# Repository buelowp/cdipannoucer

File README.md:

# Cobalt Digigal IP turnout control state announcer
The goal of this project is to provide a simple mechanism to report the realtime state of a Cobal Digital IP turnout control motor to loconet. For brevity, Cobalt Digital IP is reduced to CDIP in my work.

## Design
The Cobalt motor is really nice, it's a self contained DCC design and is reasonably robust. Not the quietest, but it works, and it works well with Digitrax and JMRI. However, because it's DCC only, JMRI has no mechanism for requesting state from the motor. This means, at startup, or if something outside of Loconet changes the turnout state, JMRI does not know that it happened. I like it when I see my layout in JMRI in the correct state. I have a 4 turnout cross over and two turnouts which gate reverse loops which are automated

So, basically, I chose this as a low impact HW/SW project I could do to solve the problem. I'm learning how to do HW as a long term software engineer by trade, and enjoy doing small projects with MCU's. This may not be very useful to very many people, but it's fun and I'm looking forward to using it on my layout which has about 30 turnouts in a 19'x19' snaking layout.

This will not do loconet forwarding, and you can't daisy chain. I started to think for the cost, it's pry just smarter to use a UP7 without the faceplate which gives you 4 reliable ports for ~16USD. While adding the HW here would have been cheaper, the cost and complexity made it less interesting to me. I may put it back in later as I get better a loconet circuitry. I removed the daisy chain option, even though that's effectively free, as you can't infinitely chain non boosted devices together, and I didn't want to keep track of how many were connected.

This design makes use of Seeed Studio XIAO modules. I love these things. They are pretty cheap overall, tiny, and you can swap different modules on the same carrier. So, my design uses the Pico MCU because I don't want to include WiFi in my design. My basement layout is pretty far from the nearest router, and I don't want to suck up a lot of the router's attention for these when turned on. However, without changing the hardware, or changing the board size, anyone could use the ESP32 if they choose to. The benefit there might be MQTT and adding a webserver to assign DCC addresses without recompiling the firmware.

While not yet coded up, my mechanism for knowing when to send a startup message will be based on the first Loconet traffic the board sees. As this can be DCC powered, it can also be DC powered, so triggering on when we start to see traffic would be the most beneficial in all cases.

## Requirements
* Provide Loconet messages for turnout state changes as they happen
* Provide a loconet message indicating turnout state on DCC power up
* Handle four turnouts on one board
* Run with either an ESP32 or RPi Pico
* Not require more than 8 GPIO (this one currently only uses 7, three are just there not doing much)
* Wide input voltage range
* Allow for direct connection of indicator LEDs for the turnout.
    * This allows to wire up signals as an example, without the need for extra diodes/resistors along the wire run.

### What it doesn't currently do
* Will not switch the turnout via a Loconet message
* Does not have a second Loconet port for daisy chain

## KiCad design
This is a work in progress. What I've got posted now is version 2, not yet ordered.

I built a first board based solely on a few simple schematic facts hoping they all sort of would just work. This did allow me to test the GPIO portion of the design and validate my assumptions were correct. However, version 1, which is not in git unforunately, did not work for Loconet traffic. I don't know why, but I did make a mistake in the pin assigments for the second Serial port on the XIAO Pico module. I did jumper it, but it still doesn't work. I also didn't add test points, so it's not possible for me at home to use a scope to figure out what's going on. All of those facts are fixed in the current version.

Recently, I also added the ability to use DCC for power. However, I couldn't find a way to combine the two DCC connectors at that point, so you always need a DCC input for the IO, but if you want to power via DCC, then you simply plug a DCC bus into the power connection. For this reason, that connection is no longer polarized, and it doesn't matter which way you wire it.

I also added 3 pins connected to D8, D9, and D10 in Arduino land. They have both Ground and Power pins to go with, so you can use them however you feel the urge. I would limit any GPIO access to 30ma total though, as you have 500ma from the board, but roughly 200ma is already consumed.

## KiCad notes
This design makes use of JLCPCB to source and order. The parts are identified in the BOM, and the parts that can't be assembled by JLCPCB are marked as such (the red X). I used a plugin to get the parts from

https://github.com/CDFER/JLCPCB-Kicad-Library

Which cannot at this time be installed automatically. Follow the directions on the README.

I also use the JLCPCB Fab extension which can be installed directly from the Extensions dialog.

# Notes
* The orientation of the DCC inputs into the Digital IP does matter. I assume for this device that DCC Rail A as labeled coming out of a Digitrax command station is the outer most pin 1 in the diagram below. If you reverse and put DCC Rail B into that slot, you either have to reverse Rail A and B inputs for the DCC Input terminal or update the code to account for the direction messages being backwards. Note, if you reverse using DCC address 197, you must also reverse the direction. This can be done by setting the CDIP inverted boolean to true.

* This is DC only, but takes up to 30V as input. The reason for this is that I have a 15V DC power bus running with the DCC bus to power some of the Digitrax devices in use (mostly PM74's). For the length of those conductors, even at 16Ga, you get some voltage drop and this should allow the boards to not worry about that.

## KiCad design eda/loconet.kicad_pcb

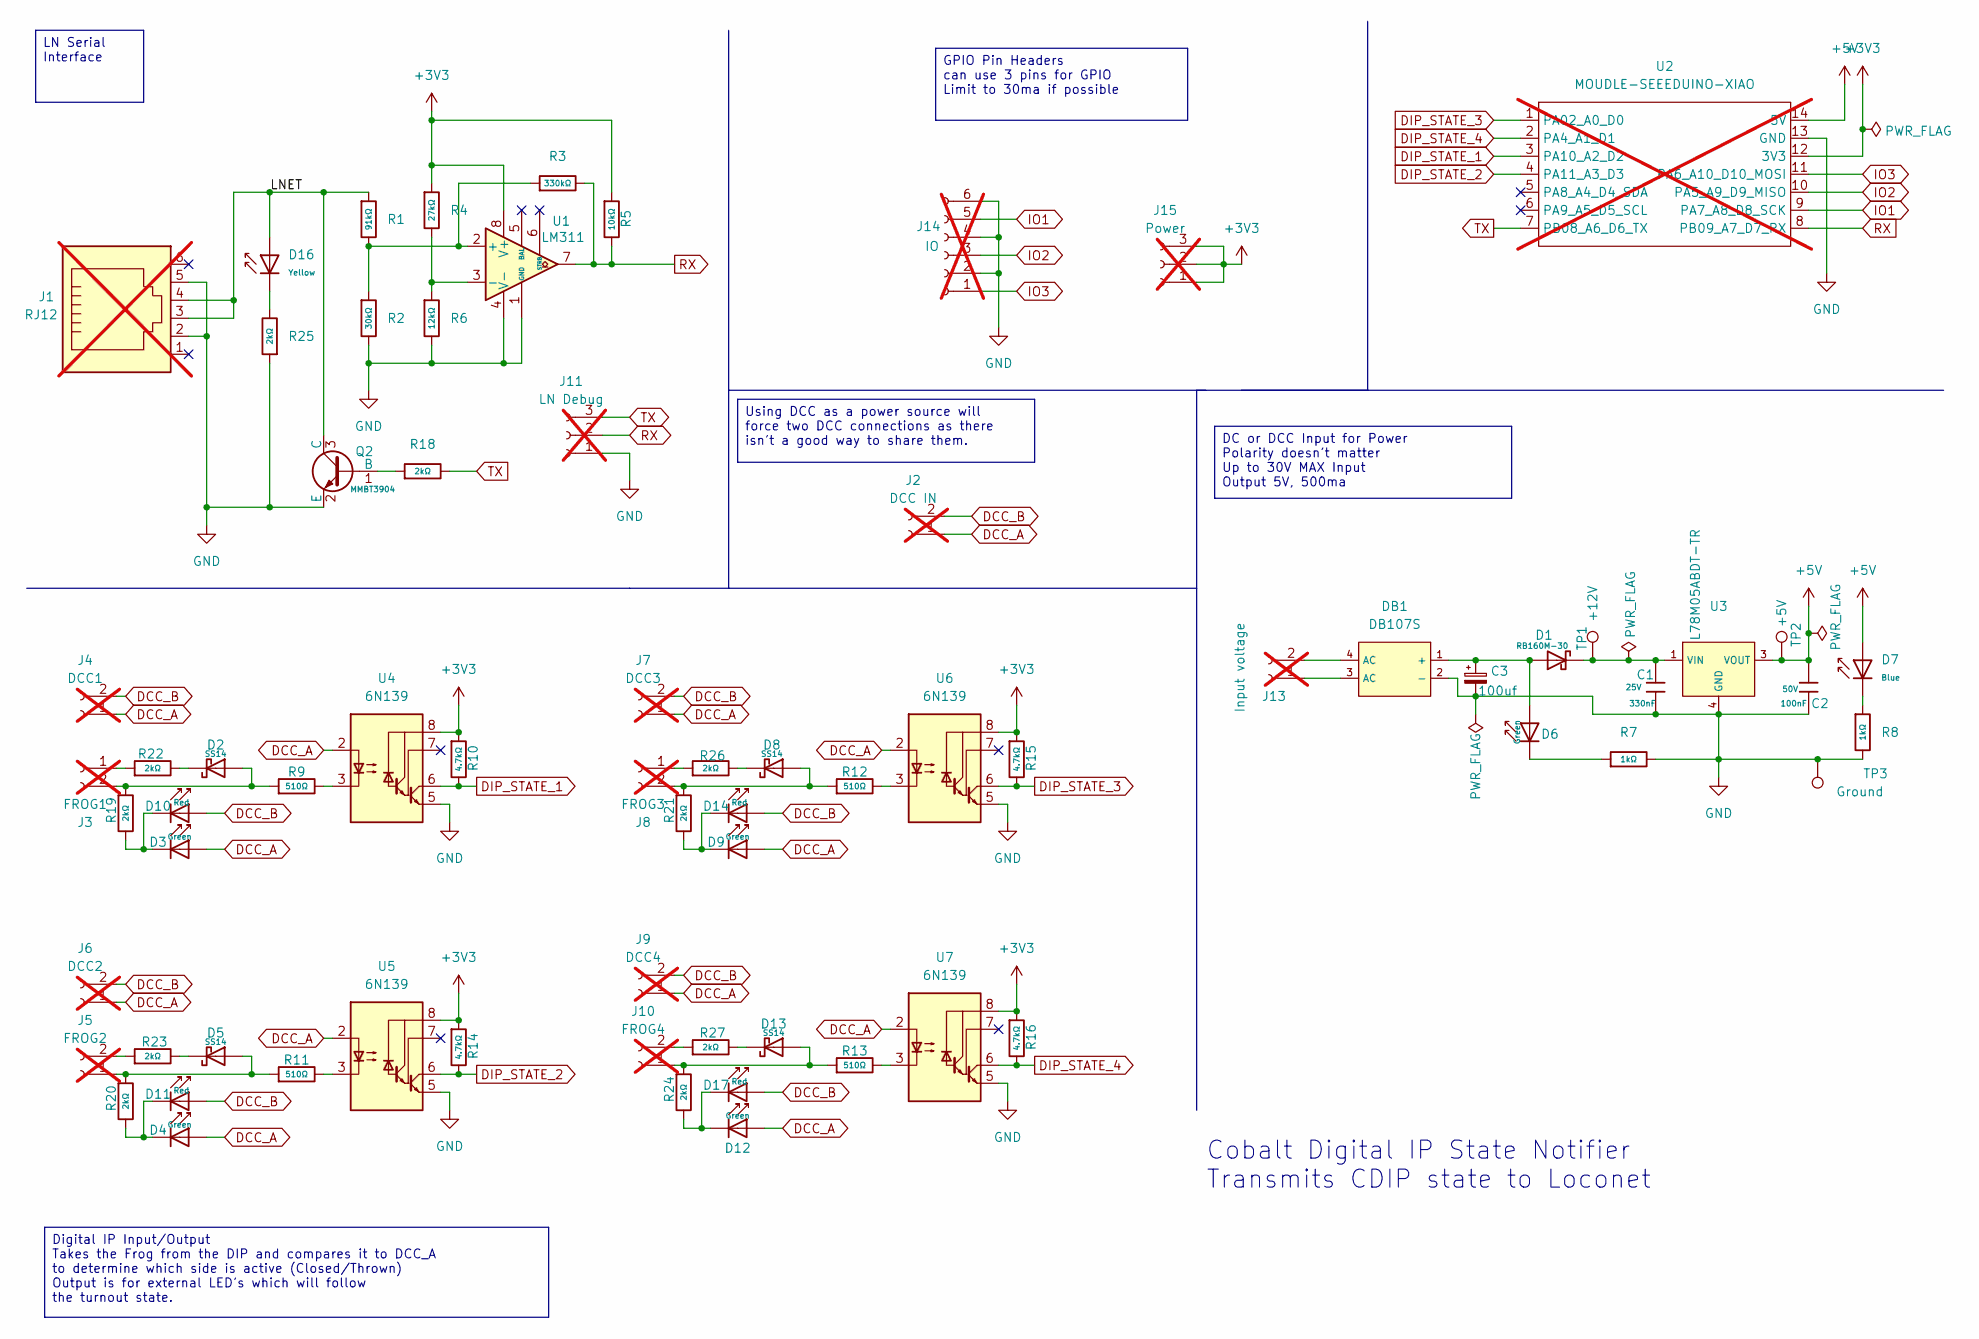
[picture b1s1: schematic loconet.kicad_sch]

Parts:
C1: 330nF; C_0603; Voltage Rated 25V; Tolerance ±10%; Part 0603B334K250NT; LCSC C1615
C2: 100nF; C_0603; Voltage Rated 50V; Tolerance ±10%; Part CC0603KRX7R9BB104; LCSC C14663
C3: 100uf; CP_Radial_D5.0mm_P2.50mm
D1: RB160M-30; D_SOD-123; Forward Voltage (Vf@If) 480mV@1A; Reverse Voltage (Vr) 30V; Part RB160M-30; LCSC C7502715
D2, D5, D8, D13: SS14; D_SMA; Forward Voltage (Vf@If) 550mV@1A; Reverse Voltage (Vr) 40V; Part SS14; LCSC C2480
D3, D4, D6, D9, D12: Green; D_0603; Part 19-217/GHC-YR1S2/6T; LCSC C2986059
D7: Blue; D_0603; Part 19-217/BHC-ZL1M2RY/6T; LCSC C2986058
D10, D11, D14, D17: Red; D_0603; Part KT-0603R; LCSC C2286
D16: Yellow; D_0603; Part 19-213/Y2C-CQ2R2L/3T(CY); LCSC C72038
DB1: DB107S; DBS_L8.2-W6.4-P5.10-LS10.0-BL; Reverse Voltage (Vr) 1kV; Forward Voltage (Vf@If) 1.1V@1A; Part DB107S; LCSC C5377
J1: RJ12; RJ25_Wayconn_MJEA-660X1_Horizontal; not fitted
J2: DCC IN; TerminalBlock_Phoenix_MKDS-1,5-2-5.08_1x02_P5.08mm_Horizont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; not fitted
J3: FROG1; TerminalBlock_Phoenix_MKDS-1,5-2-5.08_1x02_P5.08mm_Horizont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; not fitted
J4: DCC1; TerminalBlock_Phoenix_MKDS-1,5-2-5.08_1x02_P5.08mm_Horizont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; not fitted
J5: FROG2; TerminalBlock_Phoenix_MKDS-1,5-2-5.08_1x02_P5.08mm_Horizont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; not fitted
J6: DCC2; TerminalBlock_Phoenix_MKDS-1,5-2-5.08_1x02_P5.08mm_Horizont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; not fitted
J7: DCC3; TerminalBlock_Phoenix_MKDS-1,5-2-5.08_1x02_P5.08mm_Horizont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; not fitted
J8: FROG3; TerminalBlock_Phoenix_MKDS-1,5-2-5.08_1x02_P5.08mm_Horizont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; not fitted
J9: DCC4; TerminalBlock_Phoenix_MKDS-1,5-2-5.08_1x02_P5.08mm_Horizont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; not fitted
J10: FROG4; TerminalBlock_Phoenix_MKDS-1,5-2-5.08_1x02_P5.08mm_Horizont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; not fitted
J11: LN Debug; PinHeader_1x03_P2.54mm_Vertical; not fitted
J13: Input voltage; TerminalBlock_Phoenix_MKDS-1,5-2-5.08_1x02_P5.08mm_Horizont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; not fitted
J14: IO; PinHeader_2x03_P2.54mm_Vertical; not fitted
J15: Power; PinHeader_1x03_P2.54mm_Vertical; not fitted
Q2: MMBT3904; Q_SOT-23; Part MMBT3904; LCSC C7420353
R1: 91kΩ; R_0603; Overload Voltage (Max) 75V; Tolerance ±1%; Part 0603WAF9102T5E; LCSC C23265
R2: 30kΩ; R_0603; Overload Voltage (Max) 75V; Tolerance ±1%; Part 0603WAF3002T5E; LCSC C22984
R3: 330kΩ; R_0603; Overload Voltage (Max) 75V; Tolerance ±1%; Part 0603WAF3303T5E; LCSC C23137
R4: 27kΩ; R_0603; Overload Voltage (Max) 75V; Tolerance ±1%; Part 0603WAF2702T5E; LCSC C22967
R5: 10kΩ; R_0603; Overload Voltage (Max) 75V; Tolerance ±1%; Part 0603WAF1002T5E; LCSC C25804
R6: 12kΩ; R_0603; Overload Voltage (Max) 75V; Tolerance ±1%; Part 0603WAF1202T5E; LCSC C22790
R7, R8: 1kΩ; R_0402; Overload Voltage (Max) 50V; Tolerance ±1%; Part 0402WGF1001TCE; LCSC C11702
R9, R11, R12, R13: 510Ω; R_0603; Overload Voltage (Max) 75V; Tolerance ±1%; Part 0603WAF5100T5E; LCSC C23193
R10, R14, R15, R16: 4.7kΩ; R_0402; Overload Voltage (Max) 50V; Tolerance ±1%; Part 0402WGF4701TCE; LCSC C25900
R18, R22, R23, R25, R26, R27: 2kΩ; R_0402; Overload Voltage (Max) 50V; Tolerance ±1%; Part 0402WGF2001TCE; LCSC C4109
R19, R20, R21, R24: 2kΩ; R_0805; Overload Voltage (Max) 150V; Tolerance ±1%; Part 0805W8F2001T5E; LCSC C17604
TP1: +12V; TestPoint_Pad_1.5x1.5mm
TP2: +5V; TestPoint_Pad_1.5x1.5mm
TP3: Ground; TestPoint_Pad_1.5x1.5mm
U1: LM311; SOIC-8_L4.9-W3.9-P1.27-LS6.0-BL; LCSC C231850
U2: MOUDLE-SEEEDUINO-XIAO; MOUDLE14P-2.54-21X17.8MM; not fitted
U3: L78M05ABDT-TR; TO-252-2_L6.5-W6.1-P4.58-LS10.0-TL; Output Voltage 5V; Part L78M05ABDT-TR; LCSC C58069
U4, U5, U6, U7: 6N139; SOP-8_6.605x9.655mm_P2.54mm; LCSC C42186

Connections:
+3V3: J15.1, J15.2, J15.3, R4.1, R5.1, R10.1, R14.1, R15.1, R16.1, U1.8 (V+), U2.12 (3V3), U4.8 (VCC), U5.8 (VCC), U6.8 (VCC), U7.8 (VCC); also elsewhere on the board
+5V: C2.1, D7.2, TP2.1, U2.14 (5V), U3.3 (VOUT)
/LNET: D16.2, J1.3, J1.4, Q2.3 (C), R1.1
DCC_A: D3.2, D4.2, D9.2, D12.2, J2.1, J4.1, J6.1, J7.1, J9.1, U4.2 (C1), U5.2 (C1), U6.2 (C1), U7.2 (C1)
DCC_B: D10.2, D11.2, D14.2, D17.2, J2.2, J4.2, J6.2, J7.2, J9.2
DIP_STATE_1: R10.2, U2.3 (PA10_A2_D2), U4.6 (VO2)
DIP_STATE_2: R14.2, U2.4 (PA11_A3_D3), U5.6 (VO2)
DIP_STATE_3: R15.2, U2.1 (PA02_A0_D0), U6.6 (VO2)
DIP_STATE_4: R16.2, U2.2 (PA4_A1_D1), U7.6 (VO2)
GND: C1.2, C2.2, C3.2, DB1.2 (-), J1.2, J1.5, J11.1, J14.2, J14.4, J14.6, Q2.2 (E), R2.2, R6.2, R7.2, R8.2, R25.1, TP3.1, U1.1 (GND), U1.4 (V-), U2.13 (GND), U3.4 (GND), U4.5 (GND), U5.5 (GND), U6.5 (GND), U7.5 (GND)
IO1: J14.5, U2.9 (PA7_A8_D8_SCK)
IO2: J14.3, U2.10 (PA5_A9_D9_MISO)
IO3: J14.1, U2.11 (PA6_A10_D10_MOSI)
unnamed: D2.1, R22.2
unnamed: D5.1, R23.2
unnamed: D6.1, R7.1
unnamed: D7.1, R8.1
unnamed: D8.1, R26.2
unnamed: D3.1, D10.1, R19.2
unnamed: D4.1, D11.1, R20.2
unnamed: D12.1, D17.1, R24.2
unnamed: D13.1, R27.2
unnamed: D9.1, D14.1, R21.2
unnamed: D16.1, R25.2
unnamed: C3.1, D1.2, D6.2, DB1.1 (+)
unnamed: J3.1, R22.1
unnamed: D2.2, J3.2, R9.1, R19.1
unnamed: D5.2, J5.1, R11.1, R20.1
unnamed: J5.2, R23.1
unnamed: J8.1, R26.1
unnamed: D8.2, J8.2, R12.1, R21.1
unnamed: D13.2, J10.1, R13.1, R24.1
unnamed: J10.2, R27.1
unnamed: DB1.3 (AC), J13.1
unnamed: DB1.4 (AC), J13.2
unnamed: Q2.1 (B), R18.1
unnamed: R1.2, R2.1, R3.1, U1.2 (+)
unnamed: R4.2, R6.1, U1.3 (-)
unnamed: C1.1, D1.1, TP1.1, U3.1 (VIN)
unnamed: R9.2, U4.3 (C2)
unnamed: R11.2, U5.3 (C2)
unnamed: R12.2, U6.3 (C2)
unnamed: R13.2, U7.3 (C2)
RX: J11.2, R3.2, R5.2, U1.7, U2.8 (PB09_A7_D7_RX); also elsewhere on the board
TX: J11.3, R18.2, U2.7 (PB08_A6_D6_TX)

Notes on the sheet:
Cobalt Digital IP State Notifier Transmits CDIP state to Loconet
DC or DCC Input for Power Polarity doesn't matter Up to 30V MAX Input Output 5V, 500ma
Digital IP Input/Output Takes the Frog from the DIP and compares it to DCC_A to determine which side is active (Closed/Thrown) Output is for external LED's which will follow the turnout state.
GPIO Pin Headers can use 3 pins for GPIO Limit to 30ma if possible
LN Serial Interface
Using DCC as a power source will force two DCC connections as there isn't a good way to share them.

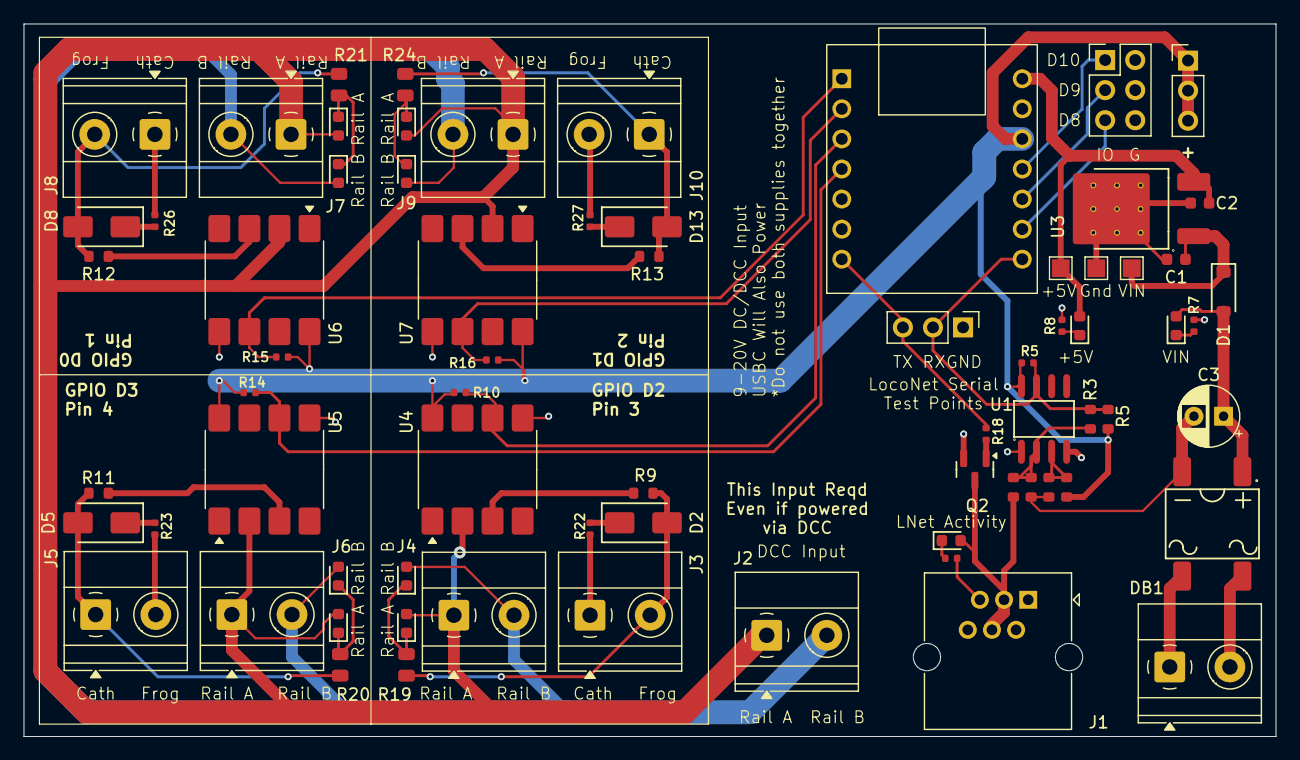
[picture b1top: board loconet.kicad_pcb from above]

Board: 2 copper layers, 105.7 x 60.2 mm, 72 parts (0 on the bottom side), 45 nets.

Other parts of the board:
R5#2: 10kΩ; R_0603

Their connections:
+3V3: R5#2.1; also elsewhere on the board
RX: R5#2.2; also elsewhere on the board

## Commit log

2025-02-24 Adding the existing files
    * Note, the hardware isn't tested, don't use it yet
2025-02-24 Quick updates
    * Adding an image
    * Updating the README
2025-02-24 Readme updates
2025-02-24 Code changes
    * Moved the timer into the class
2025-02-24 Fixups
    * I removed the additional forwarding power part of the LN schematic. I don't think I was doing it right anyway. use a UP5 instead.
2025-02-25 Updating to the latest version of the board, still in KiCad 8.
    * Bumped the README to be more readable.
    * Removed second RJ12 jack, no more forwarding.
    * Small changes to the ino.wq
2025-02-25 Fixing issues with the layout after moving to KiCad 9
2025-02-25 Design fixups
    * LDO was too limited in input voltage, switch to a part with a bigger input voltage
    * Update README
2025-02-26 Updates
    * Made it possible to power with DCC. You still need a DCC input for the IO, but you can also drive this with DCC.
    * Added some screen printing for help
    * Added 3 GPIO headers. You can connect them how you want, but they aren't protected, so don't do anything dumb.
    * updated readme
2025-02-26 README update to add GPIO notes
2025-02-26 Fixes
    * Bumped the turnout indicator LED resistor to a 125mw 0805 as the 62.5mw was likely going to be too small. This allows some headroom.
    * Updated README.
2025-02-26 README fixes
2025-02-26 Fixing a README bug
2025-02-28 checkpoint, as this board is too expensive.
2025-02-28 Fixes for cost reasons
    * Moved to a 2 layer board to try to make this cheaper
2025-02-28 Remove the barrel cap from the BOM.
2025-03-12 Mostly works now, but there is still at least one issue.
    * PCB seems to work just fine for reading inputs, and can communicate with a DCS52
    * Code has been tweaked a bit, and the inverted parameters are weird, but opposites work
    * For whatever reason, when I plug in the USB to DCS52 and connect JMRI, this all goes to hell
